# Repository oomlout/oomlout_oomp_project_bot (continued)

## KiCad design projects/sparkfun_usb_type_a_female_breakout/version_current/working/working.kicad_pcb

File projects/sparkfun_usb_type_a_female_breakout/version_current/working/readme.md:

# USB_Type_A_Female_Breakout by sparkfun  
This is a harvested standardized copy of a project from github.  
The original project can be found at:  
https://github.com/sparkfun/USB_Type_A_Female_Breakout  
Please consult that link for additional, details, files, and license information.  
Note: It was auto harvested and if the original repo had more than one board file or anything out of the ordinary the files here are likely not representative.

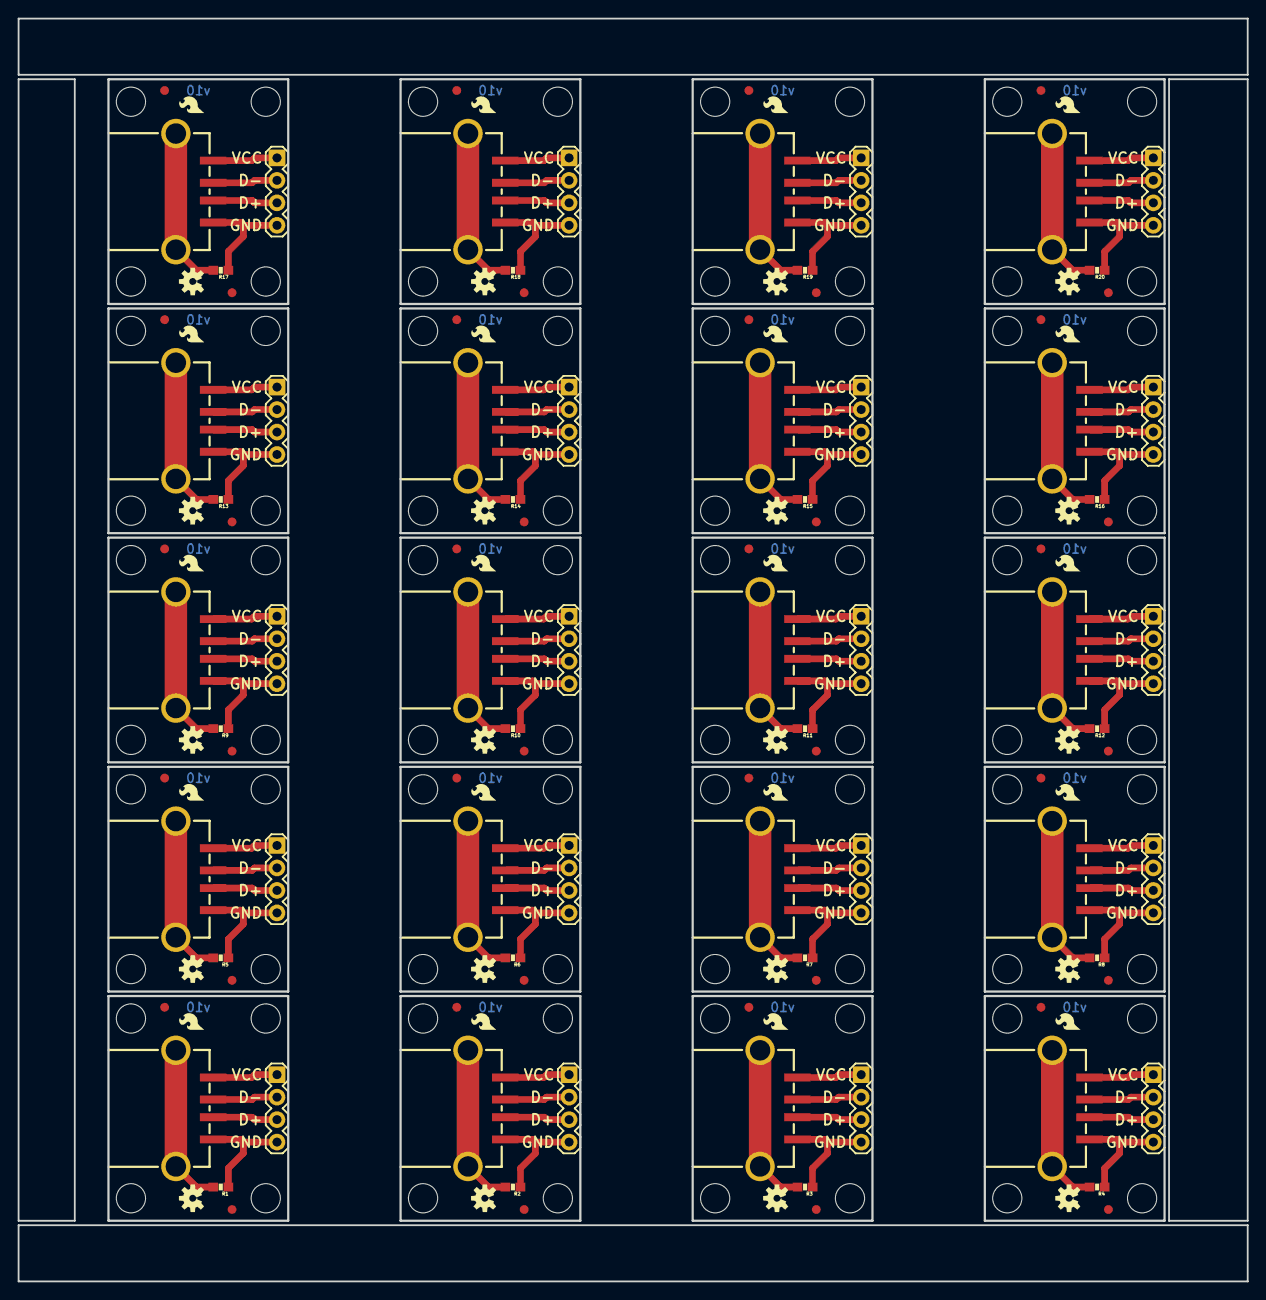
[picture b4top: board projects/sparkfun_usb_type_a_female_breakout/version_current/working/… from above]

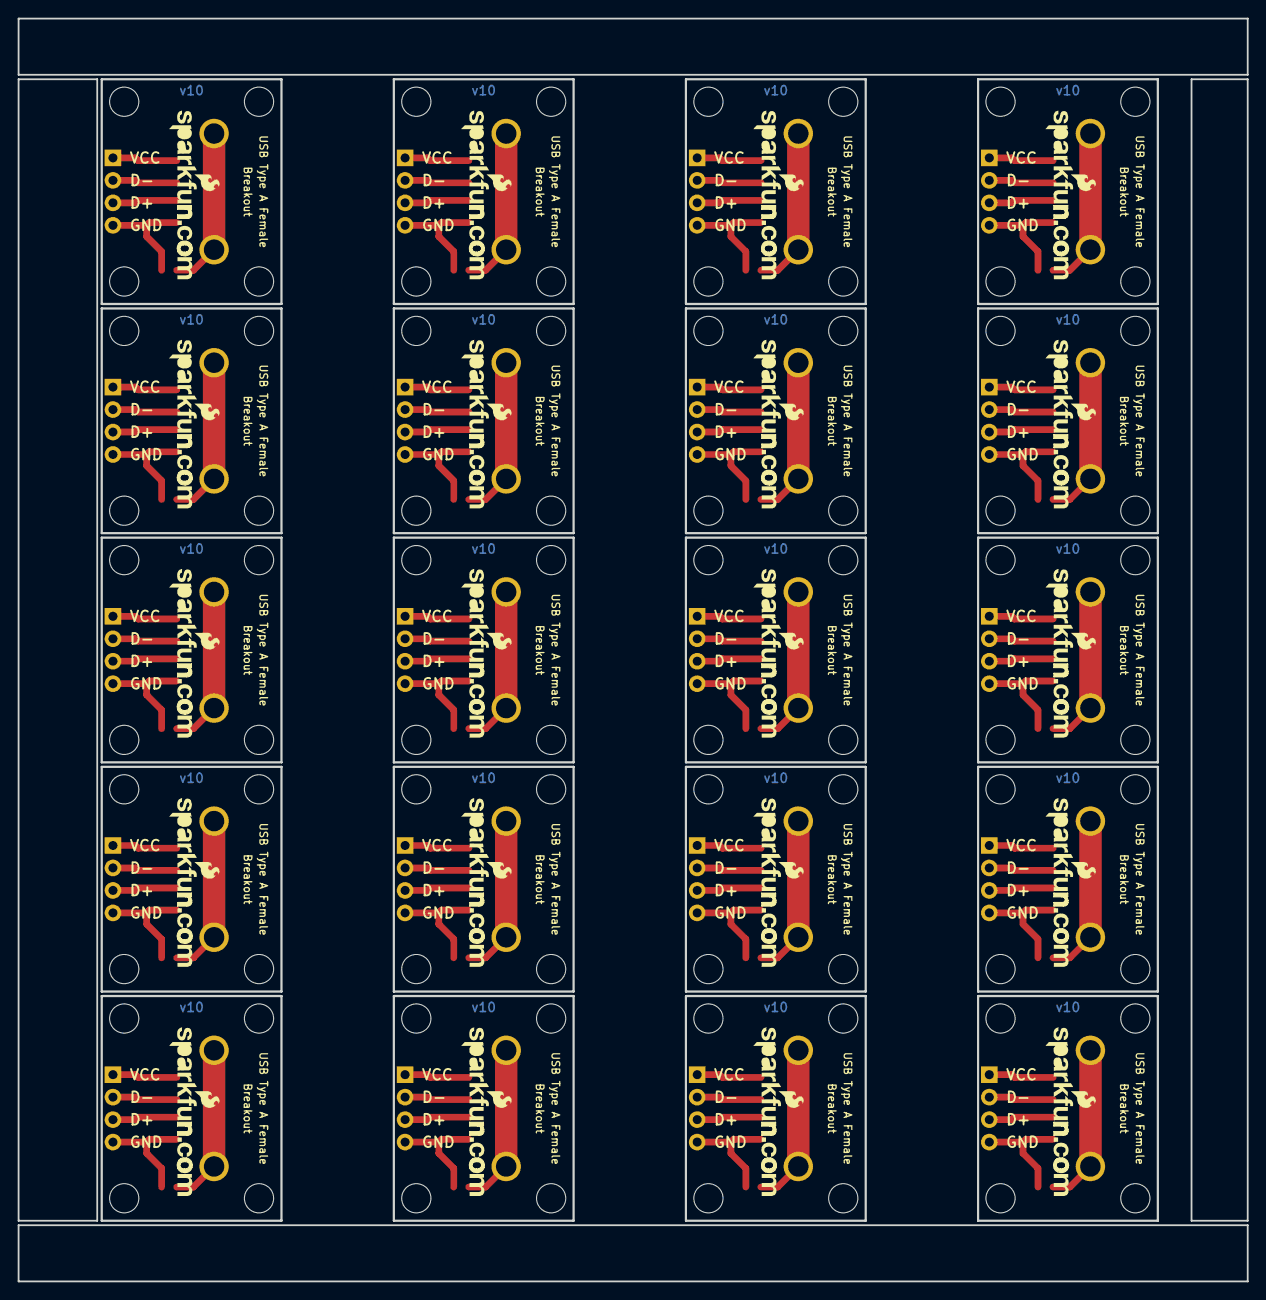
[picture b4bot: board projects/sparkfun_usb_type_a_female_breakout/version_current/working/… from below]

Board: 4 copper layers, 138.9 x 142.7 mm, 240 parts (20 on the bottom side), 100 nets.

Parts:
FID1, FID2, FID3, FID4, FID5, FID6, FID7, FID8, FID9, FID10, FID11, FID12, FID13, FID14, FID15, FID16, FID17, FID18, FID19, FID20, FID21, FID22, FID23, FID24, FID25, FID26, FID27, FID28, FID29, FID30, FID31, FID32, FID33, FID34, FID35, FID36, FID37, FID38, FID39, FID40: FIDUCIAL1X2; FIDUCIAL-1X2
JP1, JP3, JP5, JP7, JP9, JP11, JP13, JP15, JP17, JP19, JP21, JP23, JP25, JP27, JP29, JP31, JP33, JP35, JP37, JP39: USB+SHIELDUSB-A-S-NOSILK-FEMALE; USB-A-S-NOSILK-FEMALE
JP2, JP4, JP6, JP8, JP10, JP12, JP14, JP16, JP18, JP20, JP22, JP24, JP26, JP28, JP30, JP32, JP34, JP36, JP38, JP40: 1X04
LOGO1, LOGO4, LOGO7, LOGO10, LOGO13, LOGO16, LOGO19, LOGO22, LOGO25, LOGO28, LOGO31, LOGO34, LOGO37, LOGO40, LOGO43, LOGO46, LOGO49, LOGO52, LOGO55, LOGO58: LOGO-SFENEW; SFE-NEW-WEBLOGO
LOGO2, LOGO5, LOGO8, LOGO11, LOGO14, LOGO17, LOGO20, LOGO23, LOGO26, LOGO29, LOGO32, LOGO35, LOGO38, LOGO41, LOGO44, LOGO47, LOGO50, LOGO53, LOGO56, LOGO59: OSHW-LOGOS; OSHW-LOGO-S
LOGO3, LOGO6, LOGO9, LOGO12, LOGO15, LOGO18, LOGO21, LOGO24, LOGO27, LOGO30, LOGO33, LOGO36, LOGO39, LOGO42, LOGO45, LOGO48, LOGO51, LOGO54, LOGO57, LOGO60: LOGO-SFESK; SFE-LOGO-FLAME
R1, R2, R3, R4, R5, R6, R7, R8, R9, R10, R11, R12, R13, R14, R15, R16, R17, R18, R19, R20: 0; 0603-RES
STANDOFF1, STANDOFF2, STANDOFF3, STANDOFF4, STANDOFF5, STANDOFF6, STANDOFF7, STANDOFF8, STANDOFF9, STANDOFF10, STANDOFF11, STANDOFF12, STANDOFF13, STANDOFF14, STANDOFF15, STANDOFF16, STANDOFF17, STANDOFF18, STANDOFF19, STANDOFF20, STANDOFF21, STANDOFF22, STANDOFF23, STANDOFF24, STANDOFF25, STANDOFF26, STANDOFF27, STANDOFF28, STANDOFF29, STANDOFF30, STANDOFF31, STANDOFF32, STANDOFF33, STANDOFF34, STANDOFF35, STANDOFF36, STANDOFF37, STANDOFF38, STANDOFF39, STANDOFF40, STANDOFF41, STANDOFF42, STANDOFF43, STANDOFF44, STANDOFF45, STANDOFF46, STANDOFF47, STANDOFF48, STANDOFF49, STANDOFF50, STANDOFF51, STANDOFF52, STANDOFF53, STANDOFF54, STANDOFF55, STANDOFF56, STANDOFF57, STANDOFF58, STANDOFF59, STANDOFF60, STANDOFF61, STANDOFF62, STANDOFF63, STANDOFF64, STANDOFF65, STANDOFF66, STANDOFF67, STANDOFF68, STANDOFF69, STANDOFF70, STANDOFF71, STANDOFF72, STANDOFF73, STANDOFF74, STANDOFF75, STANDOFF76, STANDOFF77, STANDOFF78, STANDOFF79, STANDOFF80: STAND-OFF

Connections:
D+: JP1.D+, JP2.3
D+1: JP3.D+, JP4.3
D+2: JP5.D+, JP6.3
D+3: JP7.D+, JP8.3
D+4: JP9.D+, JP10.3
D+5: JP11.D+, JP12.3
D+6: JP13.D+, JP14.3
D+7: JP15.D+, JP16.3
D+8: JP17.D+, JP18.3
D+9: JP19.D+, JP20.3
D+10: JP21.D+, JP22.3
D+11: JP23.D+, JP24.3
D+12: JP25.D+, JP26.3
D+13: JP27.D+, JP28.3
D+14: JP29.D+, JP30.3
D+15: JP31.D+, JP32.3
D+16: JP33.D+, JP34.3
D+17: JP35.D+, JP36.3
D+18: JP37.D+, JP38.3
D+19: JP39.D+, JP40.3
D-: JP1.D-, JP2.2
D-1: JP3.D-, JP4.2
D-2: JP5.D-, JP6.2
D-3: JP7.D-, JP8.2
D-4: JP9.D-, JP10.2
D-5: JP11.D-, JP12.2
D-6: JP13.D-, JP14.2
D-7: JP15.D-, JP16.2
D-8: JP17.D-, JP18.2
D-9: JP19.D-, JP20.2
D-10: JP21.D-, JP22.2
D-11: JP23.D-, JP24.2
D-12: JP25.D-, JP26.2
D-13: JP27.D-, JP28.2
D-14: JP29.D-, JP30.2
D-15: JP31.D-, JP32.2
D-16: JP33.D-, JP34.2
D-17: JP35.D-, JP36.2
D-18: JP37.D-, JP38.2
D-19: JP39.D-, JP40.2
GND: JP1.GND, JP2.4, R1.1
GND1: JP3.GND, JP4.4, R2.1
GND2: JP5.GND, JP6.4, R3.1
GND3: JP7.GND, JP8.4, R4.1
GND4: JP9.GND, JP10.4, R5.1
GND5: JP11.GND, JP12.4, R6.1
GND6: JP13.GND, JP14.4, R7.1
GND7: JP15.GND, JP16.4, R8.1
GND8: JP17.GND, JP18.4, R9.1
GND9: JP19.GND, JP20.4, R10.1
GND10: JP21.GND, JP22.4, R11.1
GND11: JP23.GND, JP24.4, R12.1
GND12: JP25.GND, JP26.4, R13.1
GND13: JP27.GND, JP28.4, R14.1
GND14: JP29.GND, JP30.4, R15.1
GND15: JP31.GND, JP32.4, R16.1
GND16: JP33.GND, JP34.4, R17.1
GND17: JP35.GND, JP36.4, R18.1
GND18: JP37.GND, JP38.4, R19.1
GND19: JP39.GND, JP40.4, R20.1
unnamed: JP1.S1, JP1.S2, R1.2
unnamed: JP3.S1, JP3.S2, R2.2
unnamed: JP5.S1, JP5.S2, R3.2
unnamed: JP7.S1, JP7.S2, R4.2
unnamed: JP9.S1, JP9.S2, R5.2
unnamed: JP11.S1, JP11.S2, R6.2
unnamed: JP13.S1, JP13.S2, R7.2
unnamed: JP15.S1, JP15.S2, R8.2
unnamed: JP17.S1, JP17.S2, R9.2
unnamed: JP19.S1, JP19.S2, R10.2
unnamed: JP21.S1, JP21.S2, R11.2
unnamed: JP23.S1, JP23.S2, R12.2
unnamed: JP25.S1, JP25.S2, R13.2
unnamed: JP27.S1, JP27.S2, R14.2
unnamed: JP29.S1, JP29.S2, R15.2
unnamed: JP31.S1, JP31.S2, R16.2
unnamed: JP33.S1, JP33.S2, R17.2
unnamed: JP35.S1, JP35.S2, R18.2
unnamed: JP37.S1, JP37.S2, R19.2
unnamed: JP39.S1, JP39.S2, R20.2
VCC: JP1.VBUS, JP2.1
VCC1: JP3.VBUS, JP4.1
VCC2: JP5.VBUS, JP6.1
VCC3: JP7.VBUS, JP8.1
VCC4: JP9.VBUS, JP10.1
VCC5: JP11.VBUS, JP12.1
VCC6: JP13.VBUS, JP14.1
VCC7: JP15.VBUS, JP16.1
VCC8: JP17.VBUS, JP18.1
VCC9: JP19.VBUS, JP20.1
VCC10: JP21.VBUS, JP22.1
VCC11: JP23.VBUS, JP24.1
VCC12: JP25.VBUS, JP26.1
VCC13: JP27.VBUS, JP28.1
VCC14: JP29.VBUS, JP30.1
VCC15: JP31.VBUS, JP32.1
VCC16: JP33.VBUS, JP34.1
VCC17: JP35.VBUS, JP36.1
VCC18: JP37.VBUS, JP38.1
VCC19: JP39.VBUS, JP40.1

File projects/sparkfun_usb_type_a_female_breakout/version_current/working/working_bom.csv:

"Id";"Designator";"Footprint";"Quantity";"Designation";"Supplier and ref";
1;"STANDOFF18,STANDOFF12,STANDOFF66,STANDOFF27,STANDOFF79,STANDOFF8,STANDOFF19,STANDOFF46,STANDOFF21,STANDOFF29,STANDOFF45,STANDOFF48,STANDOFF23,STANDOFF59,STANDOFF61,STANDOFF53,STANDOFF30,STANDOFF40,STANDOFF50,STANDOFF36,STANDOFF41,STANDOFF58,STANDOFF14,STANDOFF60,STANDOFF76,STANDOFF4,STANDOFF24,STANDOFF3,STANDOFF63,STANDOFF32,STANDOFF67,STANDOFF64,STANDOFF6,STANDOFF62,STANDOFF44,STANDOFF49,STANDOFF47,STANDOFF25,STANDOFF35,STANDOFF22,STANDOFF10,STANDOFF55,STANDOFF42,STANDOFF1,STANDOFF38,STANDOFF11,STANDOFF56,STANDOFF70,STANDOFF2,STANDOFF71,STANDOFF74,STANDOFF9,STANDOFF33,STANDOFF5,STANDOFF52,STANDOFF77,STANDOFF13,STANDOFF16,STANDOFF31,STANDOFF65,STANDOFF15,STANDOFF43,STANDOFF69,STANDOFF28,STANDOFF26,STANDOFF39,STANDOFF57,STANDOFF54,STANDOFF20,STANDOFF37,STANDOFF75,STANDOFF80,STANDOFF7,STANDOFF17,STANDOFF78,STANDOFF68,STANDOFF34,STANDOFF51,STANDOFF72,STANDOFF73";"STAND-OFF";80;"STAND-OFF";;;
2;"JP21,JP19,JP9,JP3,JP15,JP27,JP17,JP11,JP37,JP31,JP25,JP1,JP33,JP39,JP5,JP35,JP29,JP7,JP13,JP23";"USB-A-S-NOSILK-FEMALE";20;"USB+SHIELDUSB-A-S-NOSILK-FEMALE";;;
3;"FID18,FID30,FID14,FID3,FID10,FID37,FID21,FID31,FID38,FID17,FID7,FID12,FID40,FID25,FID26,FID15,FID19,FID36,FID39,FID27,FID6,FID20,FID29,FID8,FID11,FID23,FID32,FID5,FID33,FID16,FID24,FID9,FID13,FID2,FID28,FID1,FID34,FID35,FID4,FID22";"FIDUCIAL-1X2";40;"FIDUCIAL1X2";;;
4;"R17,R5,R8,R16,R7,R4,R12,R2,R20,R6,R18,R1,R14,R11,R9,R13,R3,R15,R19,R10";"0603-RES";20;"0";;;
5;"LOGO9,LOGO54,LOGO3,LOGO12,LOGO30,LOGO15,LOGO45,LOGO33,LOGO51,LOGO48,LOGO6,LOGO27,LOGO36,LOGO39,LOGO18,LOGO42,LOGO57,LOGO21,LOGO60,LOGO24";"SFE-LOGO-FLAME";20;"LOGO-SFESK";;;
6;"JP34,JP32,JP40,JP10,JP2,JP16,JP14,JP6,JP4,JP30,JP22,JP26,JP36,JP38,JP24,JP20,JP8,JP18,JP12,JP28";"1X04";20;"";;;
7;"LOGO17,LOGO20,LOGO47,LOGO41,LOGO32,LOGO53,LOGO59,LOGO5,LOGO8,LOGO26,LOGO35,LOGO14,LOGO29,LOGO2,LOGO38,LOGO50,LOGO11,LOGO56,LOGO23,LOGO44";"OSHW-LOGO-S";20;"OSHW-LOGOS";;;
8;"LOGO1,LOGO13,LOGO22,LOGO34,LOGO31,LOGO40,LOGO25,LOGO19,LOGO49,LOGO55,LOGO28,LOGO46,LOGO58,LOGO16,LOGO10,LOGO7,LOGO43,LOGO4,LOGO37,LOGO52";"SFE-NEW-WEBLOGO";20;"LOGO-SFENEW";;;

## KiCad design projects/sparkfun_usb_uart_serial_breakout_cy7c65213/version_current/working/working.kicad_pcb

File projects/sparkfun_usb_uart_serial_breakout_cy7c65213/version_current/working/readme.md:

# USB_UART_Serial_Breakout-CY7C65213 by sparkfun  
This is a harvested standardized copy of a project from github.  
The original project can be found at:  
https://github.com/sparkfun/USB_UART_Serial_Breakout-CY7C65213  
Please consult that link for additional, details, files, and license information.  
Note: It was auto harvested and if the original repo had more than one board file or anything out of the ordinary the files here are likely not representative.

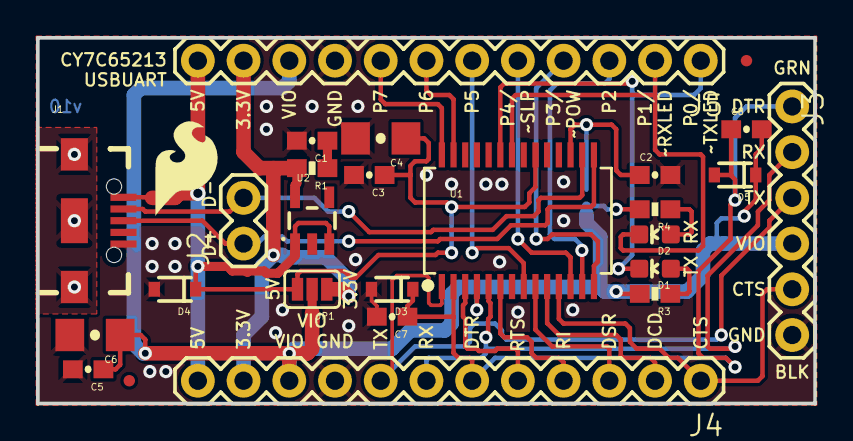
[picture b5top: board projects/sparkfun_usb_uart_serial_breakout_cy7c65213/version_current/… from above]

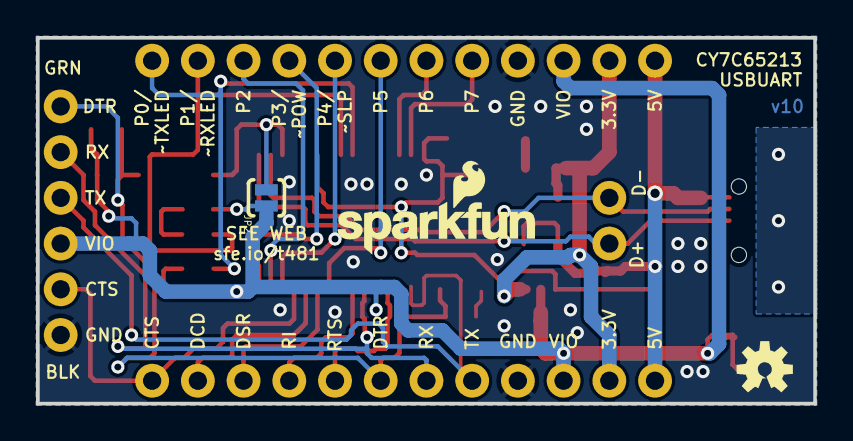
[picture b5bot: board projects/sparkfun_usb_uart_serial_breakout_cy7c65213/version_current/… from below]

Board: 4 copper layers, 43.2 x 20.3 mm, 31 parts (3 on the bottom side), 27 nets.

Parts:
C1: 2.2uF; 0603-CAP
C2: 1.0uF; 0603-CAP
C3, C5: 0.1uF; 0603-CAP
C4, C6: 4.7uF; 1206-CAP
C7, C8: 10pF; 0603-CAP
D1: RED; LED-0603
D2: GREEN; LED-0603
D3, D5: PMEG4005EJ; SOD-323
D4: 5.6V; SOD-323
FD1, FD2: FIDUCIALUFIDUCIAL; MICRO-FIDUCIAL
FRAME1: FRAME-LETTER; CREATIVE_COMMONS
J1: MICROB; USB-B-MICRO-SMD_V03
J2: 1X02
J3: FTDI_BASICPTH; FTDI_BASIC
J4, J5: 1X12
JP1: JUMPER-PAD-3-2OF3_NC_BY_PASTE; PAD-JUMPER-3-2OF3_NC_BY_PASTE_YES_SILK_FULL_BOX
JP2: JUMPER-PAD-2-NOYES_SILK; PAD-JUMPER-2-NO_YES_SILK
LOGO1: SFE_LOGO_NAME_FLAME.1_INCH; SFE_LOGO_NAME_FLAME_.1
LOGO2: OSHW-LOGOS; OSHW-LOGO-S
LOGO5: SFE_LOGO_FLAME.2_INCH; SFE_LOGO_FLAME_.2
R1: 0.27; 0603-RES
R3, R4: 1K; 0603-RES
U1: CY7C65213; SSOP28DB
U2: 3.3V; SOT23-5

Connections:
3.3V: J4.11, J5.11, JP1.1, R1.2, U2.5
5V: C3.1, C4.1, D4.C, J1.VBUS1, J4.12, J5.12, JP1.3, U1.20, U2.1, U2.3
CTS: J3.CTS, J4.1, U1.11
D+: J1.D+1, J2.1, U1.15
D-: J1.D-1, J2.2, U1.16
DCD: J4.2, U1.10
DSR: J4.3, U1.9
DTR: C7.1, C8.1, D3.C, D5.A, J3.DTR, J4.6, U1.2
GND: C1.2, C2.2, C3.2, C4.2, C5.2, C6.2, C7.2, D3.A, D4.A, J1.GND1, J3.GND, J4.9, J5.9, U1.7, U1.18, U1.21, U2.2
GPIO0: D1.C, J5.1, U1.23
GPIO1: D2.C, J5.2, U1.22
GPIO2: J5.3, U1.13
GPIO3: J5.4, U1.14
GPIO4: J5.5, U1.12
GPIO5: J5.6, U1.8
GPIO6: J5.7, U1.27
GPIO7: J5.8, U1.28
unnamed: C1.1, R1.1
unnamed: D2.A, R4.1
unnamed: D1.A, R3.1
RI: J4.4, U1.6
RTS: J4.5, U1.3
RXD: J3.RXI, J4.7, U1.5
SHIELD_POUR: J1.SHIELD1, J1.SHIELD2, J1.SHIELD3
TXD: J3.TXO, J4.8, U1.1
VCCIO: C5.1, C6.1, C8.2, D5.C, J3.VCC, J4.10, J5.10, JP1.2, JP2.1, R3.2, R4.2, U1.4
VDD: C2.1, JP2.2, U1.17

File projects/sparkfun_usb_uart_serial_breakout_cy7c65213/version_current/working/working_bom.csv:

"Id";"Designator";"Footprint";"Quantity";"Designation";"Supplier and ref";
1;"D4";"SOD-323";1;"5.6V";;;
2;"C1";"0603-CAP";1;"2.2uF";;;
3;"C5,C3";"0603-CAP";2;"0.1uF";;;
4;"U2";"SOT23-5";1;"3.3V";;;
5;"FD1,FD2";"MICRO-FIDUCIAL";2;"FIDUCIALUFIDUCIAL";;;
6;"J3";"FTDI_BASIC";1;"FTDI_BASICPTH";;;
7;"J1";"USB-B-MICRO-SMD_V03";1;"MICROB";;;
8;"R1";"0603-RES";1;"0.27";;;
9;"C6,C4";"1206-CAP";2;"4.7uF";;;
10;"LOGO5";"SFE_LOGO_FLAME_.2";1;"SFE_LOGO_FLAME.2_INCH";;;
11;"U1";"SSOP28DB";1;"CY7C65213";;;
12;"D2";"LED-0603";1;"GREEN";;;
13;"J4,J5";"1X12";2;"";;;
14;"J2";"1X02";1;"";;;
15;"FRAME1";"CREATIVE_COMMONS";1;"FRAME-LETTER";;;
16;"R4,R3";"0603-RES";2;"1K";;;
17;"JP1";"PAD-JUMPER-3-2OF3_NC_BY_PASTE_YES_SILK_FULL_BOX";1;"JUMPER-PAD-3-2OF3_NC_BY_PASTE";;;
18;"D5,D3";"SOD-323";2;"PMEG4005EJ";;;
19;"C7,C8";"0603-CAP";2;"10pF";;;
20;"D1";"LED-0603";1;"RED";;;
21;"C2";"0603-CAP";1;"1.0uF";;;
22;"JP2";"PAD-JUMPER-2-NO_YES_SILK";1;"JUMPER-PAD-2-NOYES_SILK";;;
23;"LOGO2";"OSHW-LOGO-S";1;"OSHW-LOGOS";;;
24;"LOGO1";"SFE_LOGO_NAME_FLAME_.1";1;"SFE_LOGO_NAME_FLAME.1_INCH";;;

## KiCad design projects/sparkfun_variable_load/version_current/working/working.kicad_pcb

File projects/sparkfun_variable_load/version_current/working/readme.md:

# Variable_Load by sparkfun  
This is a harvested standardized copy of a project from github.  
The original project can be found at:  
https://github.com/sparkfun/Variable_Load  
Please consult that link for additional, details, files, and license information.  
Note: It was auto harvested and if the original repo had more than one board file or anything out of the ordinary the files here are likely not representative.

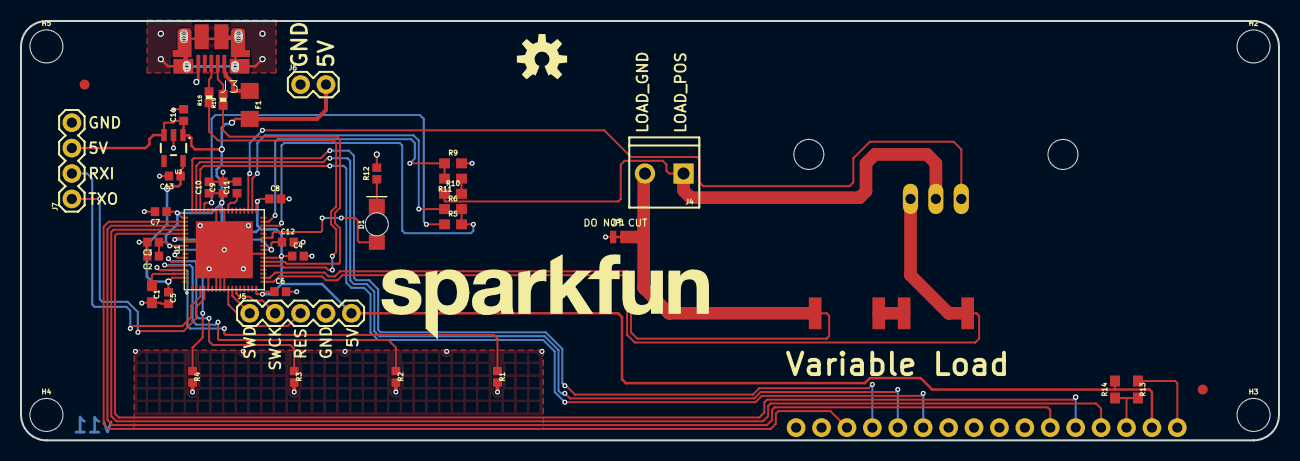
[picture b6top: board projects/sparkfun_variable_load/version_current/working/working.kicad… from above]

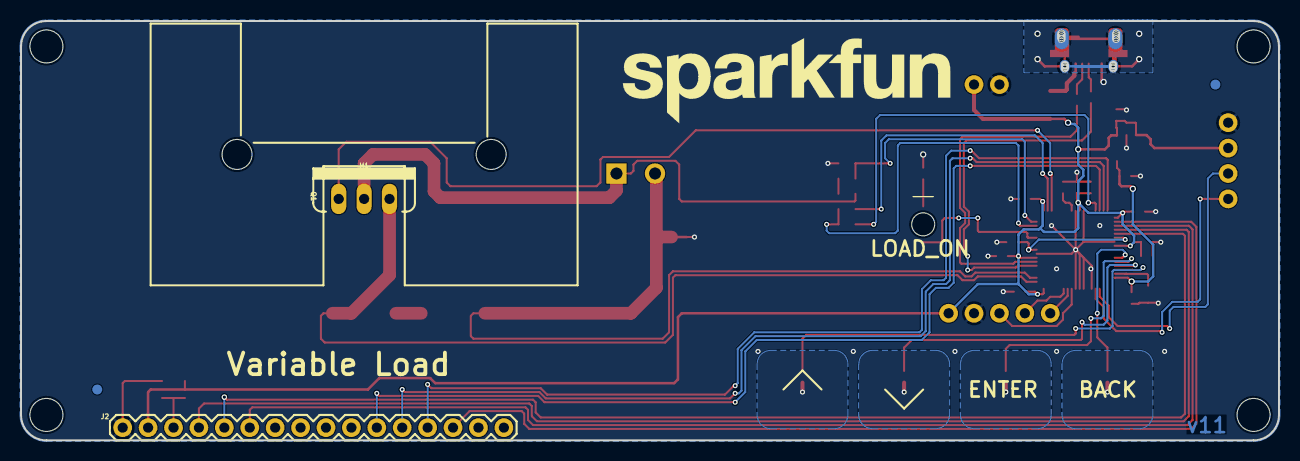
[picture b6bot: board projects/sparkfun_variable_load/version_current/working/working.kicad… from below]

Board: 4 copper layers, 125.7 x 41.9 mm, 55 parts (6 on the bottom side), 41 nets.

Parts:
C1: 2.2nF; 0603
C2, C4, C5, C6, C7, C8, C9: 0.1uF; 0402
C3, C10, C11, C12, C13, C14: 1.0uF; 0402
D1: GREEN; LED-1206-BOTTOM
F1: 6V/0.5A; 1206
FD1, FD2, FD3, FD4: FIDUCIAL1X2; FIDUCIAL-1X2
FRAME1: FRAME-LETTER; CREATIVE_COMMONS
H1: 6400BG_HEATSINK
H2, H3, H4, H5: STAND-OFF
J2: 1X16
J3: AMP FCI 10103594-0001LF; USB-MICROB-PTH
J4: SCREWTERMINAL-3.5MM-2_LOCK
J5: 1X05
J6: 1X02
J7: 1X04
JP1: JUMPER-SMT_2_NC_TRACE_NO-SILK; SMT-JUMPER_2_NC_TRACE_NO-SILK
LOGO1: OSHW-LOGOM; OSHW-LOGO-M
LOGO2, LOGO3: SFE_LOGO_NAME.3_INCH; SFE_LOGO_NAME_.3
Q1: 60V/32A/35mΩ; TO220V
R1, R2, R3, R4, R12: 560; 0402
R5, R6: 47k; 0603
R7, R8: 0.05; 2512
R9, R13: 1k; 0603
R10: 8.2k; 0603
R11: 787; 0603
R14: 4.7k; 0603
R18, R19: 22; 0402-RES
U1: CY8C5868LTI-LP039; QFN-68
U2: 3.3V; SOT23-5

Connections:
3.3V: C5.1, C13.1, U1.67, U2.5
5V: C2.1, C3.1, C4.1, C6.1, C7.1, C8.1, C9.1, C10.1, C14.1, F1.2, J2.2, J5.5, J6.2, J7.3, R14.2, U1.17, U1.24, U1.35, U1.44, U1.52, U1.59, U2.1, U2.3
CONTRAST: J2.3, R13.2, R14.1
D+: J3.D+, R18.2
D-: J3.D-, R19.2
GND: C1.2, C2.2, C3.2, C4.2, C5.2, C6.2, C7.2, C8.2, C9.2, C10.2, C11.2, C12.2, C13.2, C14.2, J2.1, J3.GND, J5.4, J6.1, J7.4, JP1.1, R9.2, R12.2, R13.1, U1.5, U1.7, U1.8, U1.9, U1.25, U1.43, U1.45, U1.58, U1.69, U2.2
GND-ISO: J4.2, JP1.2, R8.P$1, U1.19
I_SENSE_HIGH: Q1.3, R7.P$2, U1.18
I_SET: Q1.1, U1.37
I_SET_SUM: R5.2, R6.2, U1.32
LCD_D4: J2.11, U1.49
LCD_D5: J2.12, U1.50
LCD_D6: J2.13, U1.51
LCD_D7: J2.14, U1.53
LCD_E: J2.6, U1.54
LCD_RS: J2.4, U1.55
LCD_RW: J2.5, U1.56
unnamed: R1.1, U1.65
unnamed: R2.1, U1.64
unnamed: R3.1, U1.63
unnamed: R4.1, U1.62
unnamed: C1.1, U1.66
unnamed: C12.1, U1.26, U1.57
unnamed: C11.1, U1.42
unnamed: R18.1, U1.22
unnamed: R19.1, U1.23
unnamed: R5.1, U1.48
unnamed: R6.1, U1.36
unnamed: D1.A, U1.29
unnamed: D1.C, R12.1
unnamed: F1.1, J3.VBUS
unnamed: J4.1, Q1.2, R10.1
unnamed: R10.2, R11.1
unnamed: R7.P$1, R8.P$2
RXI: J7.2, U1.3
SHIELD: J3.P$1, J3.P$2, J3.P$3, J3.P$4, J3.P$6, J3.P$8, J3.P$10, J3.P$12, J3.SHEILD2, J3.SHIELD, J3.SHIELD3, J3.SHIELD4
SWDCK: J5.2, U1.12
SWDIO: J5.1, U1.11
TXO: J7.1, U1.4
V_SENSE: R9.1, R11.2, U1.33
XRES: J5.3, U1.10

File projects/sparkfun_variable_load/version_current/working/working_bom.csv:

"Id";"Designator";"Footprint";"Quantity";"Designation";"Supplier and ref";
1;"JP1";"SMT-JUMPER_2_NC_TRACE_NO-SILK";1;"JUMPER-SMT_2_NC_TRACE_NO-SILK";;;
2;"C11,C3,C12,C10,C14,C13";"0402";6;"1.0uF";;;
3;"FRAME1";"CREATIVE_COMMONS";1;"FRAME-LETTER";;;
4;"C9,C4,C8,C7,C2,C5,C6";"0402";7;"0.1uF";;;
5;"J4";"SCREWTERMINAL-3.5MM-2_LOCK";1;"";;;
6;"R2,R3,R1,R4,R12";"0402";5;"560";;;
7;"R6,R5";"0603";2;"47k";;;
8;"FD3,FD4,FD1,FD2";"FIDUCIAL-1X2";4;"FIDUCIAL1X2";;;
9;"R9,R13";"0603";2;"1k";;;
10;"H2,H4,H5,H3";"STAND-OFF";4;"STAND-OFF";;;
11;"F1";"1206";1;"6V/0.5A";;;
12;"R19,R18";"0402-RES";2;"22";;;
13;"R11";"0603";1;"787";;;
14;"R8,R7";"2512";2;"0.05";;;
15;"U2";"SOT23-5";1;"3.3V";;;
16;"R10";"0603";1;"8.2k";;;
17;"U1";"QFN-68";1;"CY8C5868LTI-LP039";;;
18;"D1";"LED-1206-BOTTOM";1;"GREEN";;;
19;"J7";"1X04";1;"";;;
20;"C1";"0603";1;"2.2nF";;;
21;"LOGO2,LOGO3";"SFE_LOGO_NAME_.3";2;"SFE_LOGO_NAME.3_INCH";;;
22;"R14";"0603";1;"4.7k";;;
23;"J5";"1X05";1;"";;;
24;"LOGO1";"OSHW-LOGO-M";1;"OSHW-LOGOM";;;
25;"J3";"USB-MICROB-PTH";1;"AMP FCI 10103594-0001LF";;;
26;"J6";"1X02";1;"";;;
27;"H1";"6400BG_HEATSINK";1;"6400BG_HEATSINK";;;
28;"J2";"1X16";1;"";;;
29;"Q1";"TO220V";1;"60V/32A/35mΩ";;;

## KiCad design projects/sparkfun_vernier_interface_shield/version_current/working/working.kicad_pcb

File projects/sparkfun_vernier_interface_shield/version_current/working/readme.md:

# Vernier_Interface_Shield by sparkfun  
This is a harvested standardized copy of a project from github.  
The original project can be found at:  
https://github.com/sparkfun/Vernier_Interface_Shield  
Please consult that link for additional, details, files, and license information.  
Note: It was auto harvested and if the original repo had more than one board file or anything out of the ordinary the files here are likely not representative.

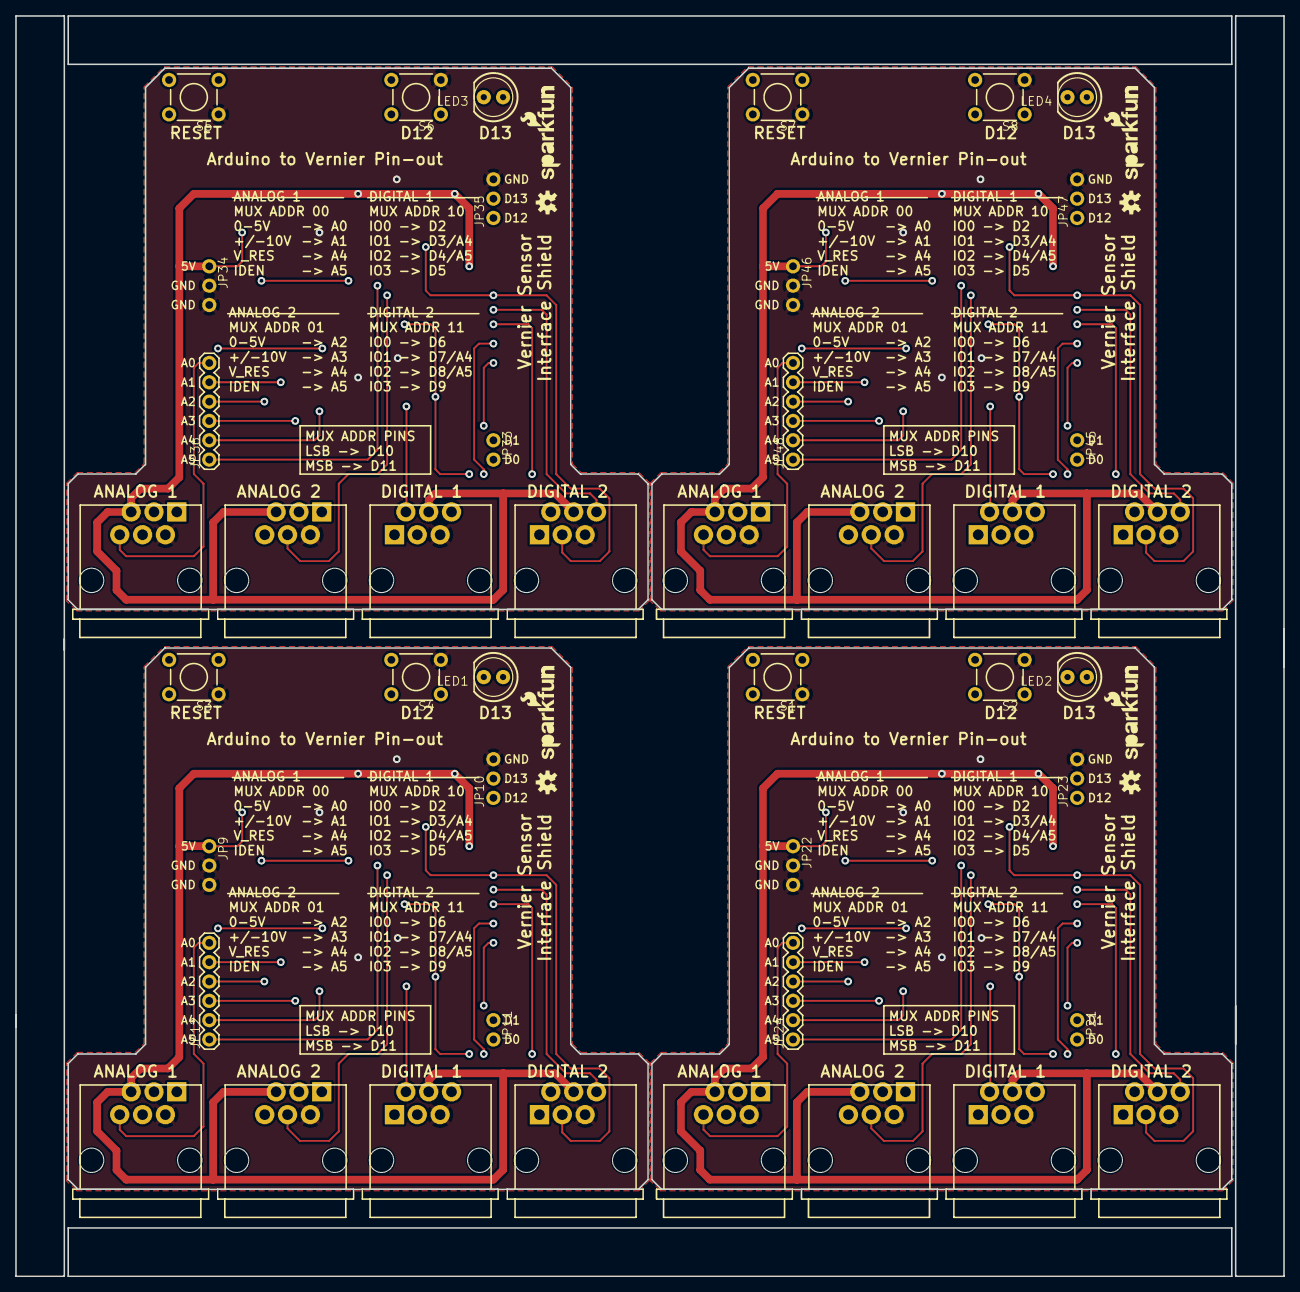
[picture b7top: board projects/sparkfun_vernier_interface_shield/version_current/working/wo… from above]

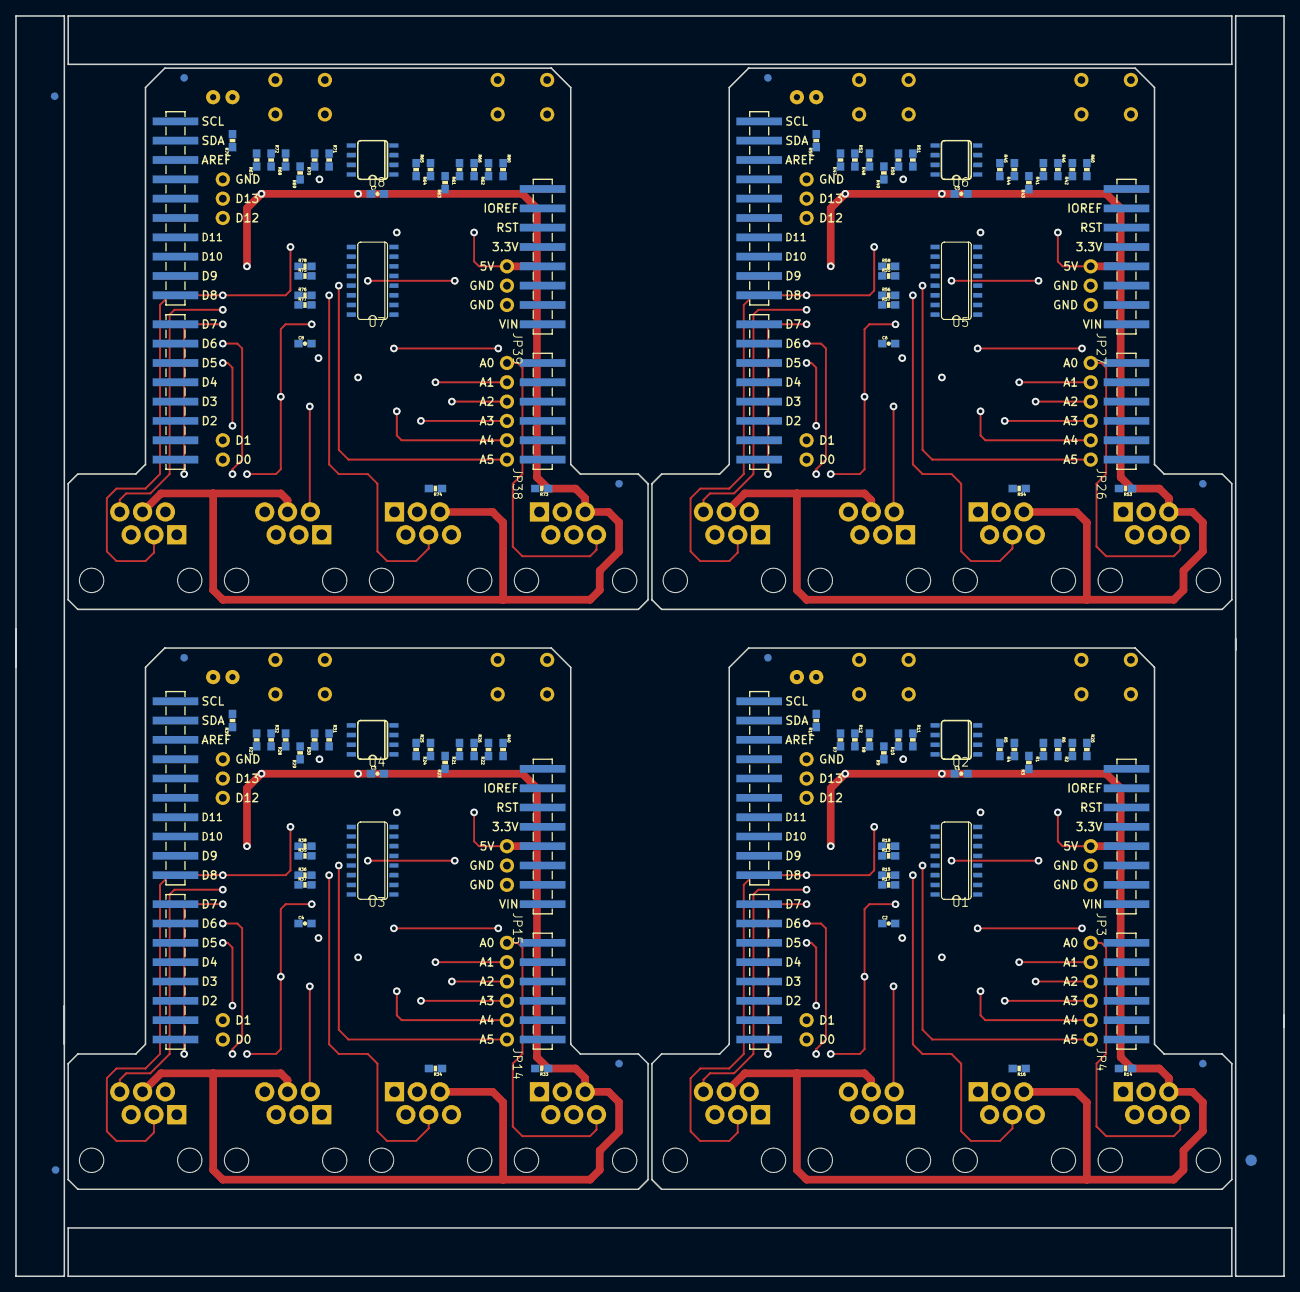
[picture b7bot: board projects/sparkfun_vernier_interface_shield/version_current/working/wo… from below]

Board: 4 copper layers, 166.6 x 165.6 mm, 179 parts (123 on the bottom side), 144 nets.

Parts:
C1, C2, C3, C4, C5, C6, C7, C8: 0.1uF; 0603-CAP
E$1: FIDUCIAL-1.5X3
E$4, E$6: FIDUCIAL-1X2
FID1, FID2, FID3, FID4, FID5, FID6, FID7, FID8: FIDUCIAL1X2; FIDUCIAL-1X2
JP1, JP13, JP25, JP37: Male; 1X10_SMD_MALE
JP2, JP3, JP15, JP16, JP27, JP28, JP39, JP40: Male; 1X08_SMD_MALE
JP4, JP14, JP26, JP38: Male; 1X06_SMD_MALE
JP5, JP6, JP18, JP19, JP30, JP31, JP42, JP43: BTA
JP7, JP8, JP17, JP20, JP29, JP32, JP41, JP44: BTD
JP9, JP10, JP22, JP23, JP34, JP35, JP46, JP47: 1X03_NO_SILK
JP11, JP21, JP33, JP45: M021X02_NO_SILK; 1X02_NO_SILK
JP12, JP24, JP36, JP48: Male; 1X06
LED1, LED2, LED3, LED4: LED5MM
LOGO1, LOGO2, LOGO3, LOGO4: OSHW-LOGOS; OSHW-LOGO-S
LOGO_1, LOGO_4, LOGO_6, LOGO_8: LOGO-SFESK; SFE-LOGO-FLAME
LOGO_2, LOGO_3, LOGO_5, LOGO_7: LOGO-SFENW2; SFE-NEW-WEB
R1, R5, R6, R7, R11, R12, R13, R15, R17, R18, R20, R21, R25, R26, R27, R31, R32, R35, R36, R37, R38, R40, R41, R45, R46, R47, R51, R52, R55, R56, R57, R58, R60, R61, R65, R66, R67, R71, R72, R75, R76, R77, R78, R80: 10K; 0603-RES
R2, R3, R4, R8, R9, R10, R22, R23, R24, R28, R29, R30, R42, R43, R44, R48, R49, R50, R62, R63, R64, R68, R69, R70: 20k; 0603-RES
R14, R16, R33, R34, R53, R54, R73, R74: 15K; 0603-RES
R19, R39, R59, R79: 330; 0603-RES
S1, S3, S5, S7: Reset; TACTILE-PTH
S2, S4, S6, S8: D12; TACTILE-PTH
U1, U3, U5, U7: 74HC4052SO; SO16
U2, U4, U6, U8: LMV358SOICT; SO08-TIGHT

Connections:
0: JP2.1, JP11.2
1: JP2.2, JP11.1
2: JP13.5, JP23.1, S2.1
3: JP16.1, JP21.2
4: JP16.2, JP21.1
5: JP13.6, JP23.2, LED2.A
5V: C1.1, C2.1, JP3.4, JP5.5, JP6.5, JP7.4, JP8.4, JP9.1, R6.2, R12.2, R13.1, R14.1, R15.1, R16.1, R17.1, R18.1, R20.2, U1.16, U2.8
5V1: C3.1, C4.1, JP15.4, JP17.4, JP18.5, JP19.5, JP20.4, JP22.1, R26.2, R32.2, R33.1, R34.1, R35.1, R36.1, R37.1, R38.1, R40.2, U3.16, U4.8
5V2: C5.1, C6.1, JP27.4, JP29.4, JP30.5, JP31.5, JP32.4, JP34.1, R46.2, R52.2, R53.1, R54.1, R55.1, R56.1, R57.1, R58.1, R60.2, U5.16, U6.8
5V3: C7.1, C8.1, JP39.4, JP41.4, JP42.5, JP43.5, JP44.4, JP46.1, R66.2, R72.2, R73.1, R74.1, R75.1, R76.1, R77.1, R78.1, R80.2, U7.16, U8.8
6: JP25.5, JP35.1, S6.1
7: JP28.1, JP33.2
8: JP28.2, JP33.1
9: JP25.6, JP35.2, LED3.A
10: JP37.5, JP47.1, S8.1
11: JP40.1, JP45.2
12: JP1.5, JP10.1, S4.1
13: JP1.6, JP10.2, LED1.A
14: JP40.2, JP45.1
15: JP37.6, JP47.2, LED4.A
A1: JP4.5, JP12.5, R5.2, U2.1
A2: JP14.2, JP24.2, U3.3
A3: JP4.3, JP12.3, R11.2, U2.7
A4: JP4.2, JP12.2, U1.3
A5: JP4.1, JP12.1, U1.13
A6: JP14.1, JP24.1, U3.13
A7: JP14.5, JP24.5, R25.2, U4.1
A8: JP14.3, JP24.3, R31.2, U4.7
A9: JP26.2, JP36.2, U5.3
A10: JP26.1, JP36.1, U5.13
A11: JP26.5, JP36.5, R45.2, U6.1
A12: JP26.3, JP36.3, R51.2, U6.7
A13: JP38.2, JP48.2, U7.3
A14: JP38.1, JP48.1, U7.13
A15: JP38.5, JP48.5, R65.2, U8.1
A16: JP38.3, JP48.3, R71.2, U8.7
AS1_AN1: JP5.1, R2.1
AS1_AN2: JP4.6, JP5.6, JP12.6
AS1_AN3: JP18.1, R22.1
AS1_AN4: JP14.6, JP18.6, JP24.6
AS1_AN5: JP30.1, R42.1
AS1_AN6: JP26.6, JP30.6, JP36.6
AS1_AN7: JP42.1, R62.1
AS1_AN8: JP38.6, JP42.6, JP48.6
AS1_AUTOID: JP5.4, R13.2, U1.12
AS1_AUTOID1: JP18.4, R35.2, U3.12
AS1_AUTOID2: JP30.4, R55.2, U5.12
AS1_AUTOID3: JP42.4, R75.2, U7.12
AS1_VRES: JP5.3, R14.2, U1.1
AS1_VRES1: JP18.3, R33.2, U3.1
AS1_VRES2: JP30.3, R53.2, U5.1
AS1_VRES3: JP42.3, R73.2, U7.1
AS2_AN1: JP6.1, R8.1
AS2_AN2: JP4.4, JP6.6, JP12.4
AS2_AN3: JP14.4, JP19.6, JP24.4
AS2_AN4: JP19.1, R28.1
AS2_AN5: JP26.4, JP31.6, JP36.4
AS2_AN6: JP31.1, R48.1
AS2_AN7: JP38.4, JP43.6, JP48.4
AS2_AN8: JP43.1, R68.1
AS2_AUTOID: JP6.4, R15.2, U1.14
AS2_AUTOID1: JP19.4, R36.2, U3.14
AS2_AUTOID2: JP31.4, R56.2, U5.14
AS2_AUTOID3: JP43.4, R76.2, U7.14
AS2_VRES: JP6.3, R16.2, U1.5
AS2_VRES1: JP19.3, R34.2, U3.5
AS2_VRES2: JP31.3, R54.2, U5.5
AS2_VRES3: JP43.3, R74.2, U7.5
D1_IO0: JP2.3, JP7.1
D1_IO1: JP2.4, JP7.2, U1.2
D1_IO2: JP2.5, JP7.3, R17.2, U1.15
D1_IO3: JP2.6, JP7.6
D1_IO4: JP16.6, JP17.6
D1_IO5: JP16.5, JP17.3, R37.2, U3.15
D1_IO6: JP16.4, JP17.2, U3.2
D1_IO7: JP16.3, JP17.1
D1_IO8: JP28.6, JP29.6
D1_IO9: JP28.5, JP29.3, R57.2, U5.15
D1_IO10: JP28.4, JP29.2, U5.2
D1_IO11: JP28.3, JP29.1
D1_IO12: JP40.6, JP41.6
D1_IO13: JP40.5, JP41.3, R77.2, U7.15
D1_IO14: JP40.4, JP41.2, U7.2
D1_IO15: JP40.3, JP41.1
D2_IO0: JP2.7, JP8.1
D2_IO1: JP2.8, JP8.2, U1.4
D2_IO2: JP1.1, JP8.3, R18.2, U1.11
D2_IO3: JP1.2, JP8.6
D2_IO4: JP13.2, JP20.6
D2_IO5: JP13.1, JP20.3, R38.2, U3.11
D2_IO6: JP16.8, JP20.2, U3.4
D2_IO7: JP16.7, JP20.1
D2_IO8: JP25.2, JP32.6
D2_IO9: JP25.1, JP32.3, R58.2, U5.11
D2_IO10: JP28.8, JP32.2, U5.4
D2_IO11: JP28.7, JP32.1
D2_IO12: JP37.2, JP44.6
D2_IO13: JP37.1, JP44.3, R78.2, U7.11
D2_IO14: JP40.8, JP44.2, U7.4
D2_IO15: JP40.7, JP44.1
GND: C1.2, C2.2, JP1.7, JP3.2, JP3.3, JP5.2, JP6.2, JP7.5, JP8.5, JP9.2, JP9.3, JP10.3, R1.1, R3.1, R7.1, R9.1, R19.1, S3.1, S4.3, U1.6, U1.7, U1.8, U2.4
GND1: C3.2, C4.2, JP13.7, JP15.2, JP15.3, JP17.5, JP18.2, JP19.2, JP20.5, JP22.2, JP22.3, JP23.3, R21.1, R23.1, R27.1, R29.1, R39.1, S1.1, S2.3, U3.6, U3.7, U3.8, U4.4
GND2: C5.2, C6.2, JP25.7, JP27.2, JP27.3, JP29.5, JP30.2, JP31.2, JP32.5, JP34.2, JP34.3, JP35.3, R41.1, R43.1, R47.1, R49.1, R59.1, S5.1, S6.3, U5.6, U5.7, U5.8, U6.4
GND3: C7.2, C8.2, JP37.7, JP39.2, JP39.3, JP41.5, JP42.2, JP43.2, JP44.5, JP46.2, JP46.3, JP47.3, R61.1, R63.1, R67.1, R69.1, R79.1, S7.1, S8.3, U7.6, U7.7, U7.8, U8.4
MUX_A0: JP1.3, U1.10
MUX_A1: JP1.4, U1.9
MUX_A2: JP13.3, U3.10
MUX_A3: JP13.4, U3.9
MUX_A4: JP25.3, U5.10
MUX_A5: JP25.4, U5.9
MUX_A6: JP37.3, U7.10
MUX_A7: JP37.4, U7.9
unnamed: R1.2, R2.2, R6.1, U2.3
unnamed: R3.2, R4.1
unnamed: R4.2, R5.1, U2.2
unnamed: R23.2, R24.1
unnamed: R9.2, R10.1
unnamed: R7.2, R8.2, R12.1, U2.5
unnamed: R10.2, R11.1, U2.6
unnamed: LED1.K, R19.2
unnamed: R21.2, R22.2, R26.1, U4.3
unnamed: R24.2, R25.1, U4.2
unnamed: R29.2, R30.1
unnamed: R27.2, R28.2, R32.1, U4.5
unnamed: R30.2, R31.1, U4.6
unnamed: LED2.K, R39.2
unnamed: R43.2, R44.1
unnamed: R41.2, R42.2, R46.1, U6.3
unnamed: R44.2, R45.1, U6.2
unnamed: R49.2, R50.1
unnamed: R47.2, R48.2, R52.1, U6.5
unnamed: R50.2, R51.1, U6.6
unnamed: LED3.K, R59.2
unnamed: R63.2, R64.1
unnamed: R61.2, R62.2, R66.1, U8.3
unnamed: R64.2, R65.1, U8.2
unnamed: R69.2, R70.1
unnamed: R67.2, R68.2, R72.1, U8.5
unnamed: R70.2, R71.1, U8.6
unnamed: LED4.K, R79.2
RESET: JP3.6, R20.1, S3.3
RESET1: JP15.6, R40.1, S1.3
RESET2: JP27.6, R60.1, S5.3
RESET3: JP39.6, R80.1, S7.3

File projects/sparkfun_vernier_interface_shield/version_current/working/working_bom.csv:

"Id";"Designator";"Footprint";"Quantity";"Designation";"Supplier and ref";
1;"JP9,JP22,JP47,JP46,JP23,JP10,JP35,JP34";"1X03_NO_SILK";8;"";;;
2;"LOGO_8,LOGO_1,LOGO_6,LOGO_4";"SFE-LOGO-FLAME";4;"LOGO-SFESK";;;
3;"S2,S6,S4,S8";"TACTILE-PTH";4;"D12";;;
4;"JP20,JP32,JP41,JP17,JP29,JP44,JP8,JP7";"BTD";8;"BTD";;;
5;"LED1,LED2,LED3,LED4";"LED5MM";4;"";;;
6;"LOGO_7,LOGO_2,LOGO_5,LOGO_3";"SFE-NEW-WEB";4;"LOGO-SFENW2";;;
7;"LOGO2,LOGO1,LOGO4,LOGO3";"OSHW-LOGO-S";4;"OSHW-LOGOS";;;
8;"JP33,JP11,JP21,JP45";"1X02_NO_SILK";4;"M021X02_NO_SILK";;;
9;"JP30,JP5,JP42,JP31,JP19,JP6,JP18,JP43";"BTA";8;"BTA";;;
10;"S1,S7,S3,S5";"TACTILE-PTH";4;"Reset";;;
11;"JP24,JP36,JP48,JP12";"1X06";4;"Male";;;
12;"R14,R74,R33,R16,R54,R34,R53,R73";"0603-RES";8;"15K";;;
13;"R42,R10,R4,R69,R70,R22,R44,R3,R68,R50,R29,R30,R23,R2,R64,R43,R28,R62,R63,R9,R49,R24,R48,R8";"0603-RES";24;"20k";;;
14;"R79,R19,R39,R59";"0603-RES";4;"330";;;
15;"R52,R75,R47,R27,R40,R20,R1,R35,R38,R76,R12,R71,R6,R18,R13,R45,R57,R72,R5,R32,R46,R61,R15,R67,R31,R17,R80,R41,R55,R65,R37,R77,R11,R60,R56,R51,R25,R21,R66,R36,R58,R78,R26,R7";"0603-RES";44;"10K";;;
16;"FID2,FID3,FID1,FID7,FID8,FID5,FID6,FID4";"FIDUCIAL-1X2";8;"FIDUCIAL1X2";;;
17;"JP27,JP39,JP3,JP2,JP28,JP15,JP16,JP40";"1X08_SMD_MALE";8;"Male";;;
18;"U1,U3,U7,U5";"SO16";4;"74HC4052SO";;;
19;"JP26,JP38,JP14,JP4";"1X06_SMD_MALE";4;"Male";;;
20;"U8,U4,U6,U2";"SO08-TIGHT";4;"LMV358SOICT";;;
21;"C7,C4,C1,C6,C5,C2,C8,C3";"0603-CAP";8;"0.1uF";;;
22;"JP13,JP1,JP25,JP37";"1X10_SMD_MALE";4;"Male";;;
23;"E$6,E$4";"FIDUCIAL-1X2";2;"";;;
24;"E$1";"FIDUCIAL-1.5X3";1;"";;;
